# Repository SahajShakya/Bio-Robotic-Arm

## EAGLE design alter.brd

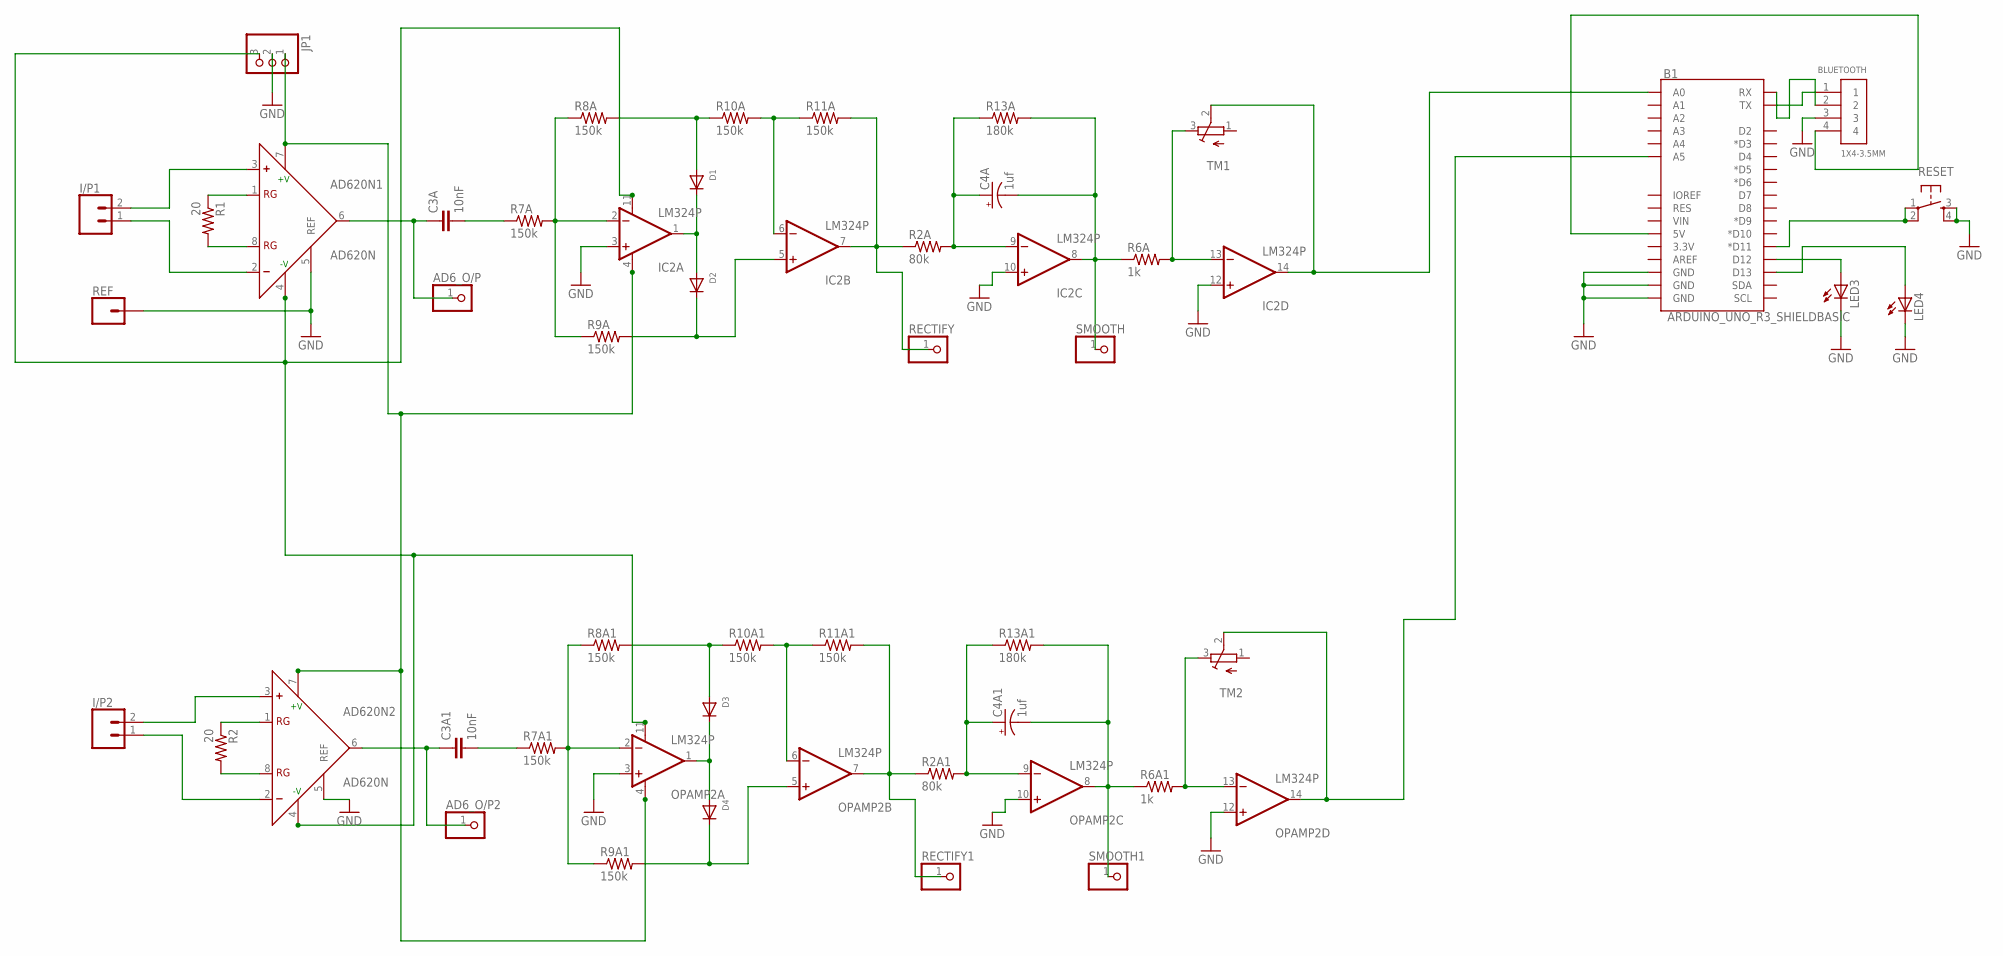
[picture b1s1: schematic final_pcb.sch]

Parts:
AD6_O/P, AD6_O/P2: PINHD-1X1; 1X01
AD620N1, AD620N2: AD620N; DIL08
B1: ARDUINO_UNO_R3_SHIELDBASIC; UNO_R3_SHIELD
BLUETOOTH: 1X4-3.5MM; 1X04-3.5MM
C3A, C3A1: 10nF; CAP-PTH-10MM
C4A, C4A1: 1uf; CPOL-RADIAL-5MM-10MM-KIT
D1, D2, D3, D4: DIODEDO-1N4148; DO-1N4148
I/P1, I/P2: CONN_02; 1X02
IC2: LM324P; DIL14
JP1: PINHD-1X3; 1X03
LED3, LED4: LED5MM
OPAMP2: LM324P; DIL14
R1, R2: 20; 0207/9
R2A, R2A1: 80k; 0207/9
R6A, R6A1: 1k; 0207/9
R7A, R7A1, R8A, R8A1, R9A, R9A1, R10A, R10A1, R11A, R11A1: 150k; 0207/9
R13A, R13A1: 180k; 0207/9
RECTIFY, RECTIFY1: PINHD-1X1; 1X01
REF: CONN_01; 1X01
RESET: TAC_SWITCHPTH; TACTILE-PTH
SMOOTH, SMOOTH1: PINHD-1X1; 1X01
TM1, TM2: TRIMPOT3386; TRIM-3386

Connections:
GND: AD620N1.5 (REF), AD620N2.5 (REF), B1.GND@0 (GND), B1.GND@1 (GND), B1.GND@2 (GND), BLUETOOTH.3, IC2.3 (+IN), IC2.10 (+IN), IC2.12 (+IN), JP1.2, LED3.K (C), LED4.K (C), OPAMP2.3 (+IN), OPAMP2.10 (+IN), OPAMP2.12 (+IN), REF.1, RESET.3, RESET.4
unnamed: AD620N1.7 (+V), AD620N2.7 (+V), IC2.4 (V+), JP1.1, OPAMP2.4 (V+)
unnamed: AD620N1.2 (-), I/P1.1
unnamed: AD620N1.3 (+), I/P1.2
unnamed: AD620N1.1 (RG), R1.1
unnamed: AD620N1.8 (RG), R1.2
unnamed: AD6_O/P.1, AD620N1.6 (OUT), C3A.1
unnamed: C3A.2, R7A.1
unnamed: IC2.2 (-IN), R7A.2, R8A.1, R9A.1
unnamed: D1.A, R8A.2, R10A.1
unnamed: D1.C, D2.A, IC2.1 (OUT)
unnamed: IC2.7 (OUT), R2A.1, R11A.2, RECTIFY.1
unnamed: IC2.6 (-IN), R10A.2, R11A.1
unnamed: C4A.+, IC2.9 (-IN), R2A.2, R13A.1
unnamed: C4A.-, IC2.8 (OUT), R6A.1, R13A.2, SMOOTH.1
unnamed: IC2.13 (-IN), R6A.2, TM1.3 (E)
unnamed: B1.A0, IC2.14 (OUT), TM1.2 (S)
unnamed: AD620N1.4 (-V), AD620N2.4 (-V), IC2.11 (V-), JP1.3, OPAMP2.11 (V-)
unnamed: AD620N2.1 (RG), R2.1
unnamed: AD620N2.8 (RG), R2.2
unnamed: AD6_O/P2.1, AD620N2.6 (OUT), C3A1.1
unnamed: C3A1.2, R7A1.1
unnamed: OPAMP2.2 (-IN), R7A1.2, R8A1.1, R9A1.1
unnamed: D3.A, R8A1.2, R10A1.1
unnamed: D3.C, D4.A, OPAMP2.1 (OUT)
unnamed: OPAMP2.7 (OUT), R2A1.1, R11A1.2, RECTIFY1.1
unnamed: OPAMP2.6 (-IN), R10A1.2, R11A1.1
unnamed: C4A1.+, OPAMP2.9 (-IN), R2A1.2, R13A1.1
unnamed: C4A1.-, OPAMP2.8 (OUT), R6A1.1, R13A1.2, SMOOTH1.1
unnamed: OPAMP2.13 (-IN), R6A1.2, TM2.3 (E)
unnamed: AD620N2.3 (+), I/P2.2
unnamed: B1.TX, BLUETOOTH.1
unnamed: B1.RX, BLUETOOTH.2
unnamed: B1.D11 (*D11), RESET.1, RESET.2
unnamed: B1.5V, BLUETOOTH.4
unnamed: B1.D12, LED3.A
unnamed: B1.D13, LED4.A
unnamed: D2.C, IC2.5 (+IN), R9A.2
unnamed: B1.A5, OPAMP2.14 (OUT), TM2.2 (S)
unnamed: D4.C, OPAMP2.5 (+IN), R9A1.2
unnamed: AD620N2.2 (-), I/P2.1

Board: 2 copper layers, 47 parts (1 on the bottom side), 41 nets, no tracks yet.

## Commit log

2023-01-30 Code
2023-01-30 Final Report
2023-01-30 code, design
2023-01-30 paper

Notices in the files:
parts and their libraries:
SparkFun-Boards: Licensing: Creative Commons ShareAlike 4.0 International - https://creativecommons.org/licenses/by-sa/4.0
